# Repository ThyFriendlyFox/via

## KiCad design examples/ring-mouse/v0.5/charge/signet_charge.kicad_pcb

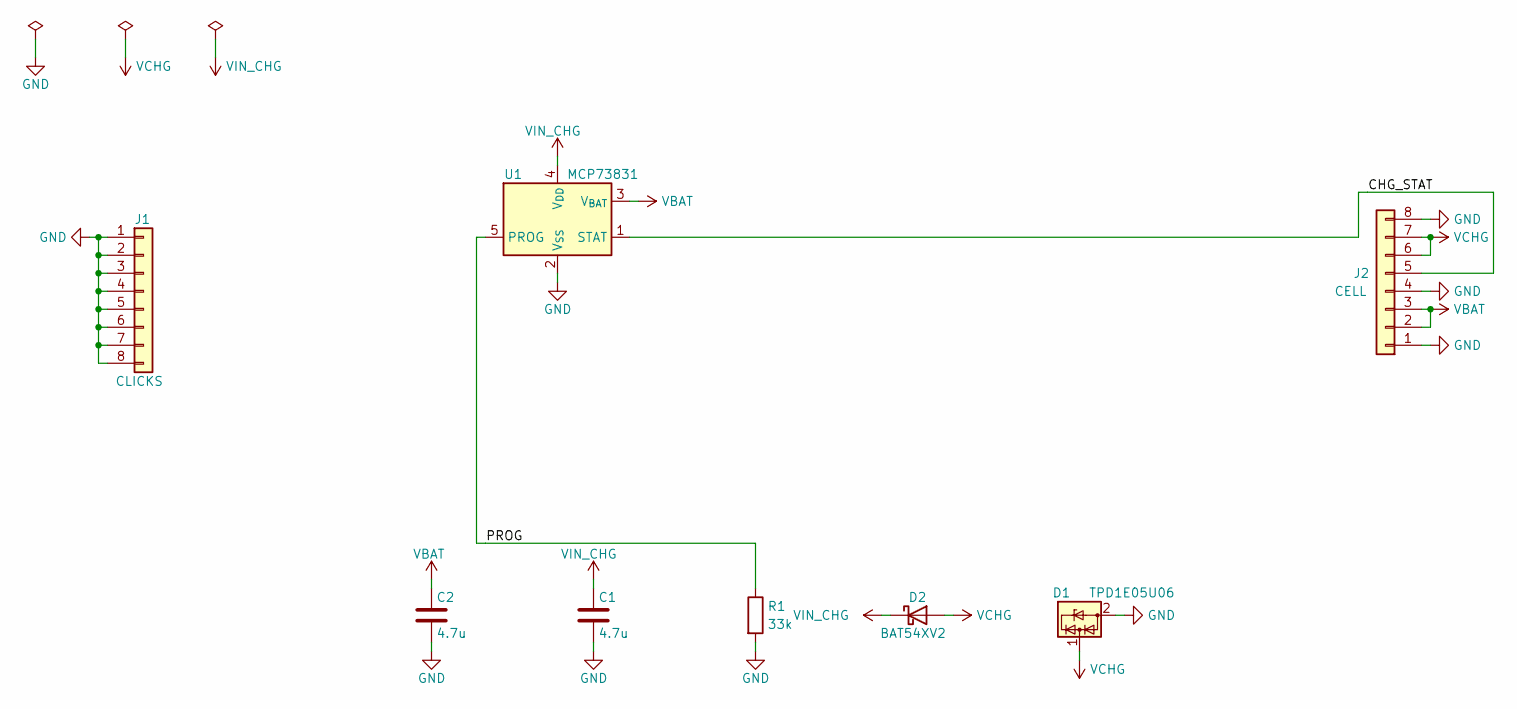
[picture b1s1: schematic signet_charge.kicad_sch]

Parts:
C1, C2: 4.7u; C_0402_1005Metric
D1: TPD1E05U06; D_SOD-523
D2: BAT54XV2; D_SOD-523
J1: CLICKS; Joint_Edge_1x08_P1.3mm
J2: CELL; Joint_Edge_1x08_P1.3mm
R1: 33k; R_0402_1005Metric
U1: MCP73831; SOT-23-5

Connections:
/CHG_STAT: J2.5, U1.1 (STAT)
/PROG: R1.1, U1.5 (PROG)
GND: C1.2, C2.2, D1.2 (GND), J1.1, J1.2, J1.3, J1.4, J1.5, J1.6, J1.7, J1.8, J2.1, J2.4, J2.8, R1.2, U1.2 (V_{SS})
VBAT: C2.1, J2.2, J2.3, U1.3 (V_{BAT})
VCHG: D1.1 (I/O), D2.2 (A), J2.6, J2.7
VIN_CHG: C1.1, D2.1 (K), U1.4 (V_{DD})

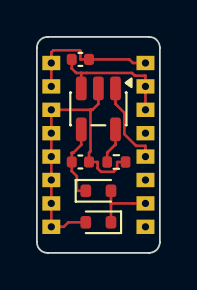
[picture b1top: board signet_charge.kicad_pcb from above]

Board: 4 copper layers, 6.8 x 12.0 mm, 8 parts (0 on the bottom side), 6 nets.

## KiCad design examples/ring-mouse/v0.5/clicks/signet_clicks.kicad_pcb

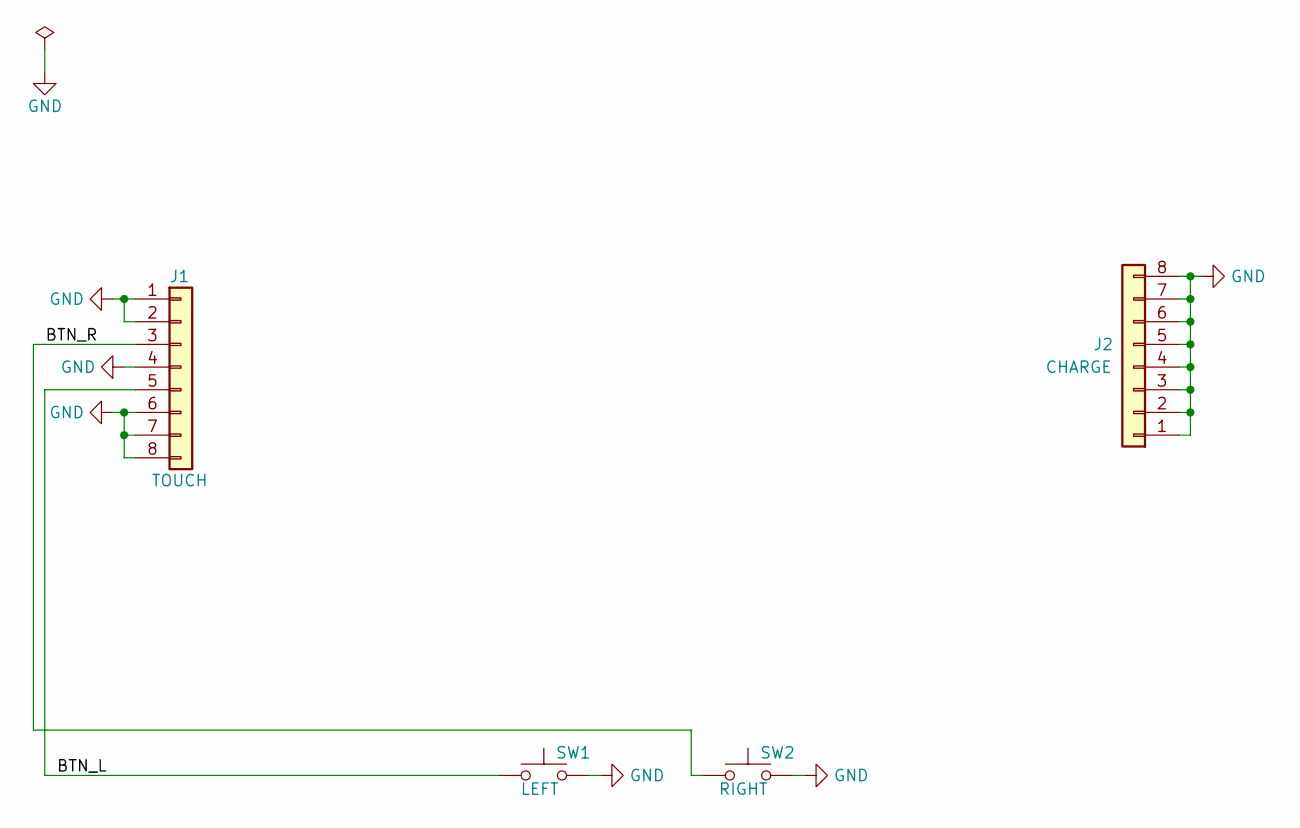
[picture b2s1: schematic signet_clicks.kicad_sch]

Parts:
J1: TOUCH; Joint_Edge_1x08_P1.3mm
J2: CHARGE; Joint_Edge_1x08_P1.3mm
SW1: LEFT; SW_Push_1P1T_NO_CK_KMR2
SW2: RIGHT; SW_Push_1P1T_NO_CK_KMR2

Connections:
/BTN_L: J1.5, SW1.1
/BTN_R: J1.3, SW2.1
GND: J1.1, J1.2, J1.4, J1.6, J1.7, J1.8, J2.1, J2.2, J2.3, J2.4, J2.5, J2.6, J2.7, J2.8, SW1.2, SW2.2

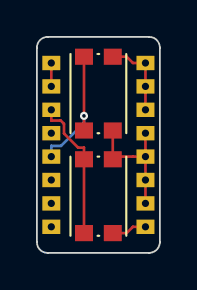
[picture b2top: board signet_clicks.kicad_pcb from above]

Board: 4 copper layers, 6.8 x 12.0 mm, 4 parts (0 on the bottom side), 3 nets.

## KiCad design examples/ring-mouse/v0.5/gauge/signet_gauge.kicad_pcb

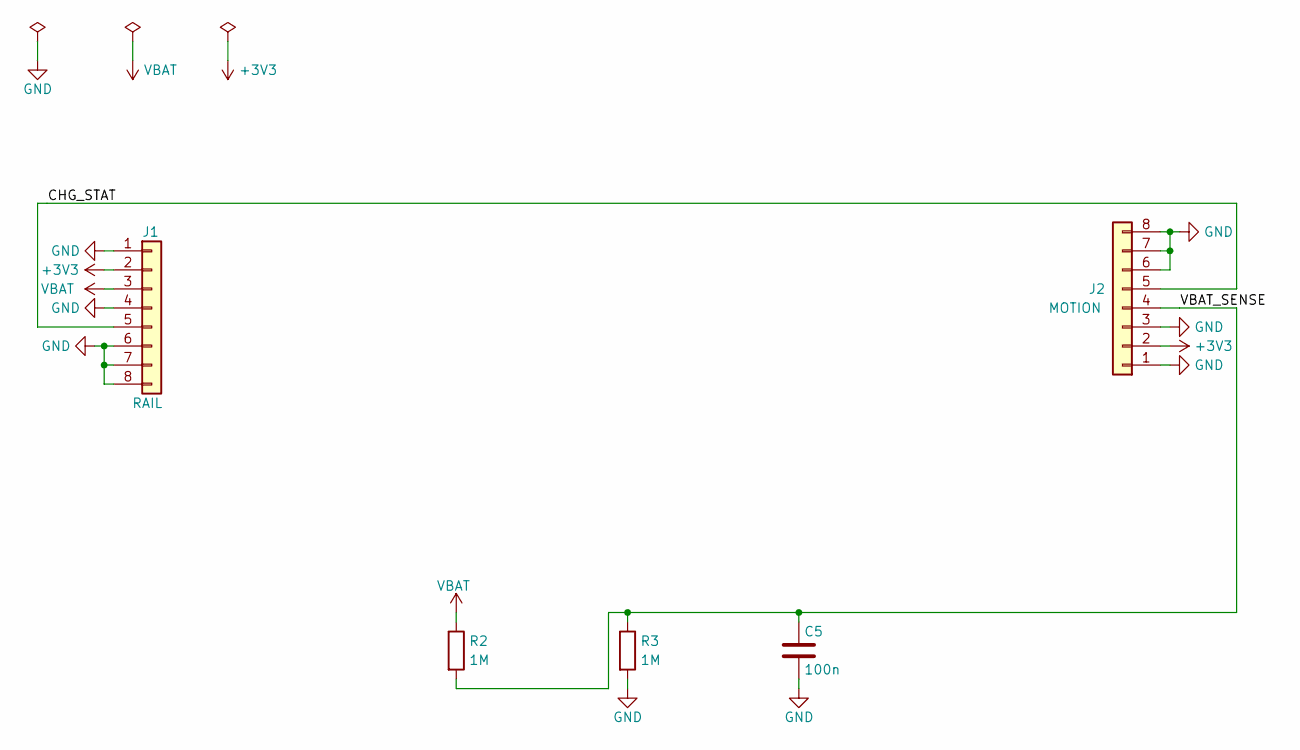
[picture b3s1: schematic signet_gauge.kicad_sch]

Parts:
C5: 100n; C_0402_1005Metric
J1: RAIL; Joint_Edge_1x08_P1.3mm
J2: MOTION; Joint_Edge_1x08_P1.3mm
R2, R3: 1M; R_0402_1005Metric

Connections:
+3V3: J1.2, J2.2
/CHG_STAT: J1.5, J2.5
/VBAT_SENSE: C5.1, J2.4, R2.2, R3.1
GND: C5.2, J1.1, J1.4, J1.6, J1.7, J1.8, J2.1, J2.3, J2.6, J2.7, J2.8, R3.2
VBAT: J1.3, R2.1

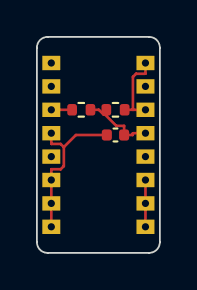
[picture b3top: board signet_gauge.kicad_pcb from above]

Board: 4 copper layers, 6.8 x 12.0 mm, 5 parts (0 on the bottom side), 5 nets.

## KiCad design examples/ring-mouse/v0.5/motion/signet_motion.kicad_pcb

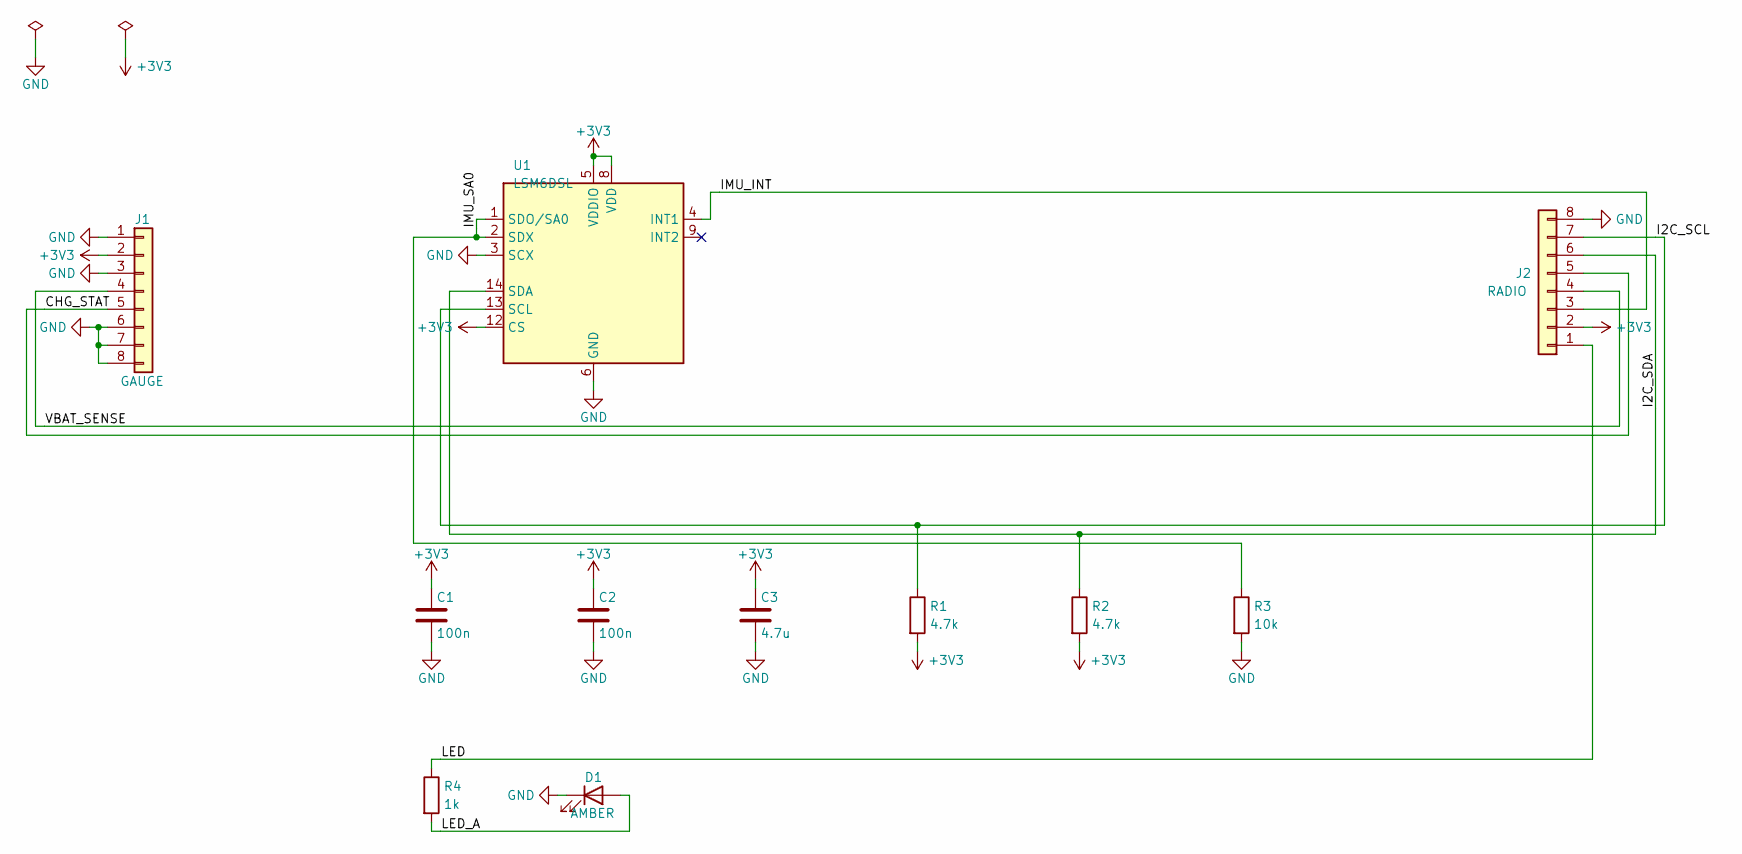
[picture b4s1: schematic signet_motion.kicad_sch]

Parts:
C1, C2: 100n; C_0402_1005Metric
C3: 4.7u; C_0402_1005Metric
D1: AMBER; LED_0402_1005Metric
J1: GAUGE; Joint_Edge_1x08_P1.3mm
J2: RADIO; Joint_Edge_1x08_P1.3mm
R1, R2: 4.7k; R_0402_1005Metric
R3: 10k; R_0402_1005Metric
R4: 1k; R_0402_1005Metric
U1: LSM6DSL; LGA-14_3x2.5mm_P0.5mm_LayoutBorder3x4y

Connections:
+3V3: C1.1, C2.1, C3.1, J1.2, J2.2, R1.2, R2.2, U1.5 (VDDIO), U1.8 (VDD), U1.12 (CS)
/CHG_STAT: J1.5, J2.5
/I2C_SCL: J2.7, R1.1, U1.13 (SCL)
/I2C_SDA: J2.6, R2.1, U1.14 (SDA)
/IMU_INT: J2.3, U1.4 (INT1)
/IMU_SA0: R3.1, U1.1 (SDO/SA0), U1.2 (SDX)
/LED: J2.1, R4.1
/LED_A: D1.2 (A), R4.2
/VBAT_SENSE: J1.4, J2.4
GND: C1.2, C2.2, C3.2, D1.1 (K), J1.1, J1.3, J1.6, J1.7, J1.8, J2.8, R3.2, U1.3 (SCX), U1.6 (GND), U1.7 (GND)

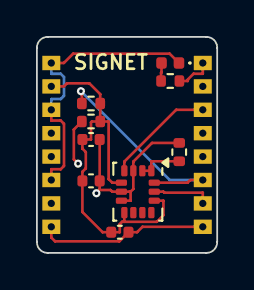
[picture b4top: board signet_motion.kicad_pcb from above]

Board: 4 copper layers, 10.0 x 12.0 mm, 11 parts (0 on the bottom side), 10 nets.

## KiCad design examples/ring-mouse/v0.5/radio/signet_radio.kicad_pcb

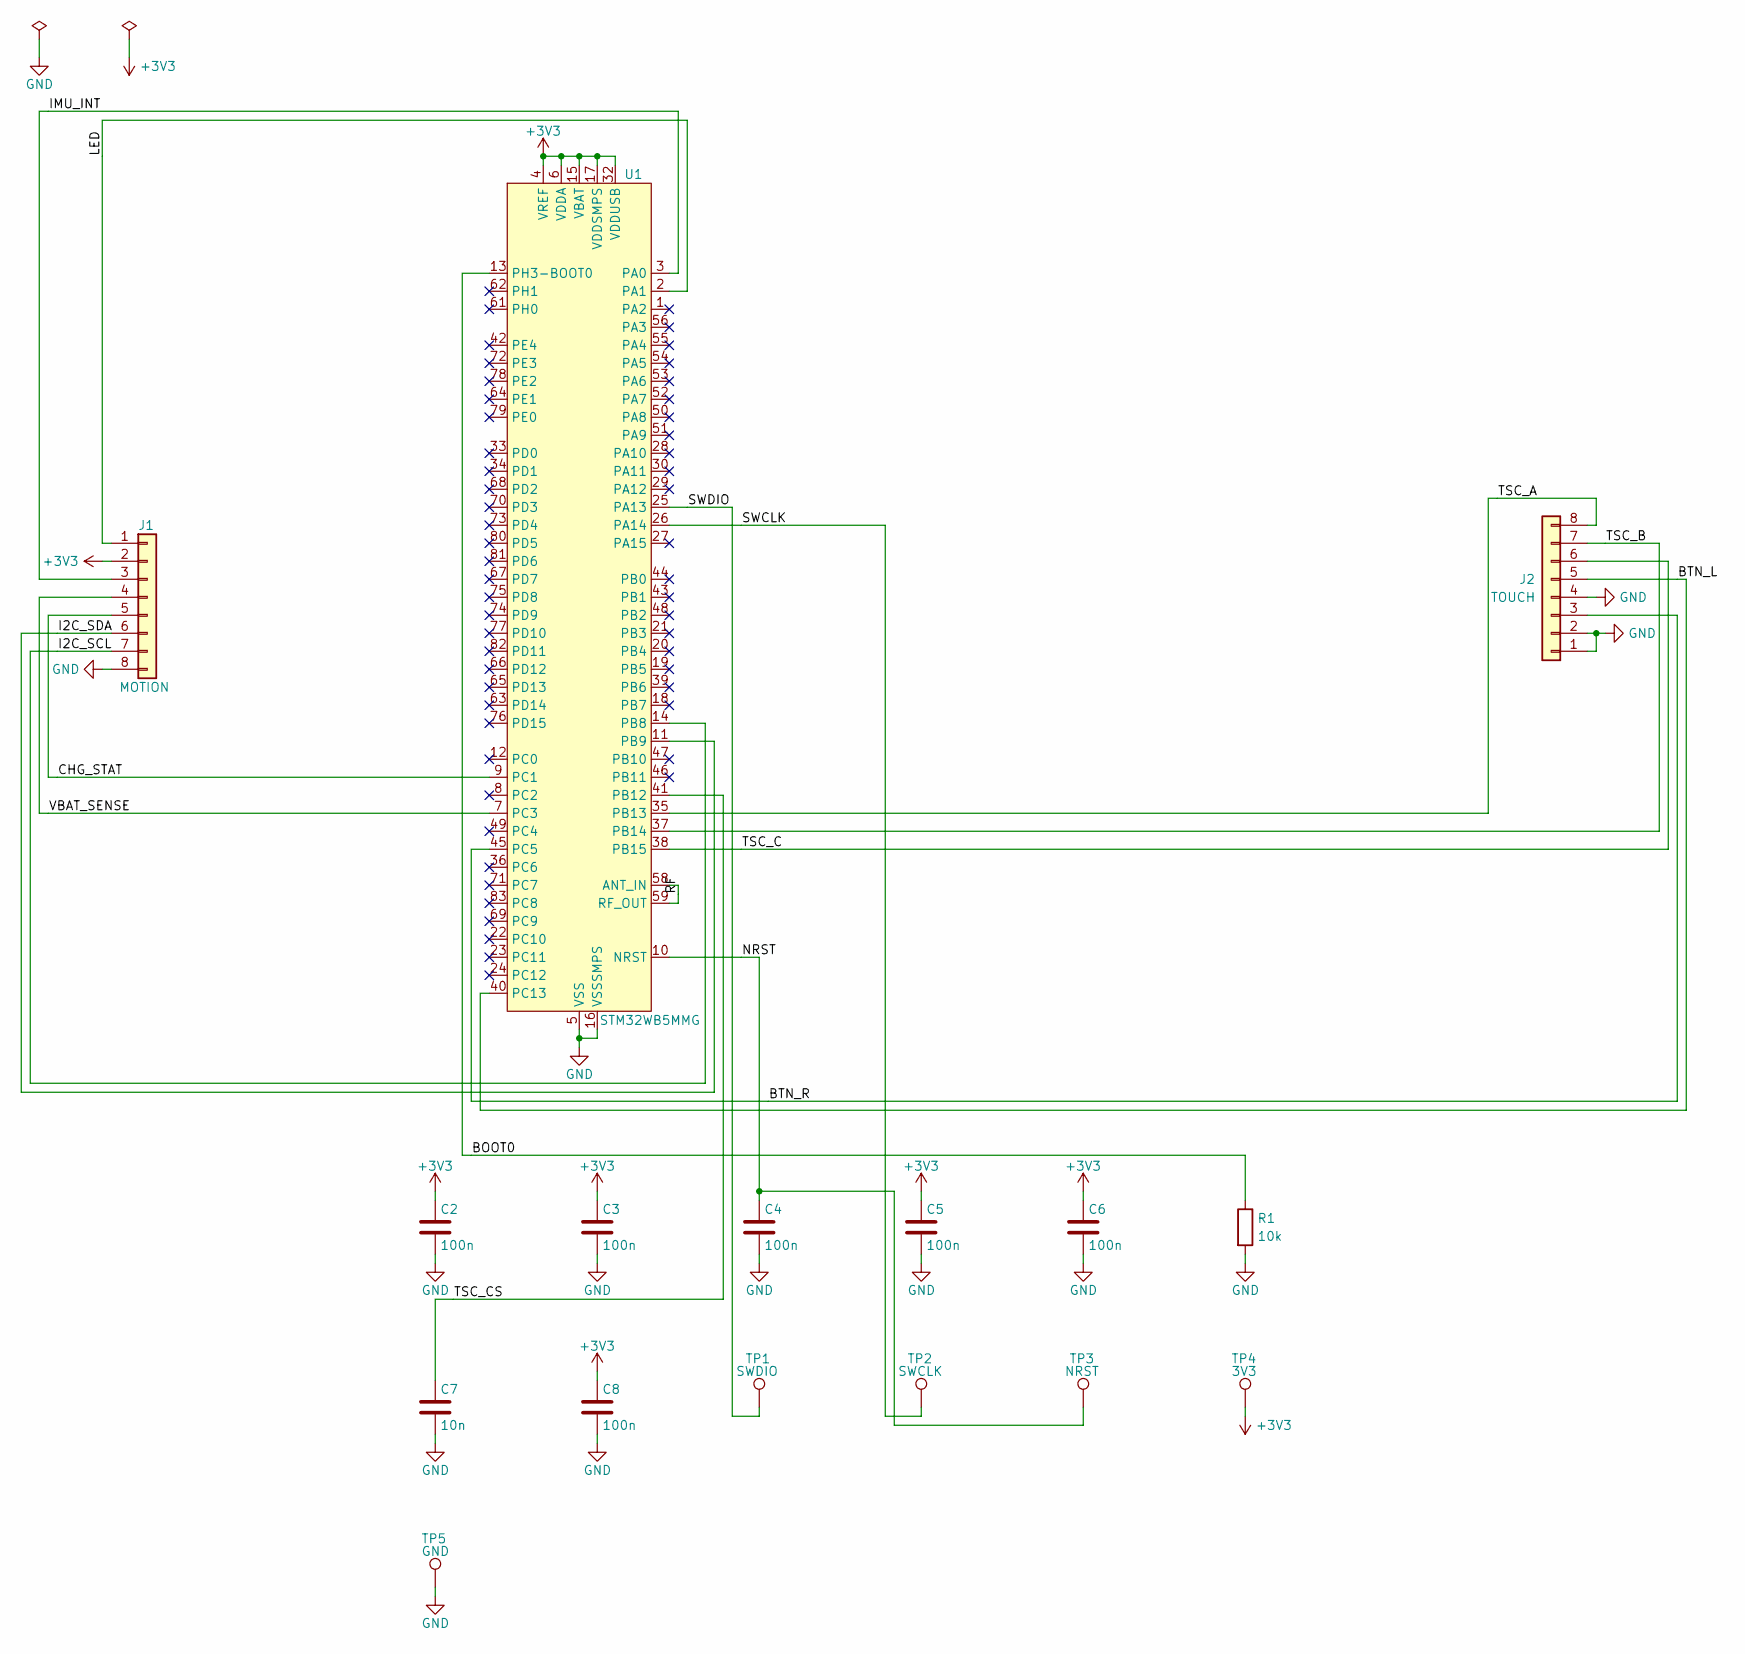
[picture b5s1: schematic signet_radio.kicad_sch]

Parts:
C2, C3, C4, C5, C6, C8: 100n; C_0201_0603Metric
C7: 10n; C_0201_0603Metric
J1: MOTION; Joint_Edge_1x08_P1.3mm
J2: TOUCH; Joint_Edge_1x08_P1.3mm
R1: 10k; R_0201_0603Metric
TP1: SWDIO; TestPoint_Pad_D1.0mm
TP2: SWCLK; TestPoint_Pad_D1.0mm
TP3: NRST; TestPoint_Pad_D1.0mm
TP4: 3V3; TestPoint_Pad_D1.0mm
TP5: GND; TestPoint_Pad_D1.0mm
U1: STM32WB5MMG; ST-SiP-LGA-86-11x7.3mm

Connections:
+3V3: C2.1, C3.1, C5.1, C6.1, C8.1, J1.2, TP4.1, U1.4 (VREF), U1.6 (VDDA), U1.15 (VBAT), U1.17 (VDDSMPS), U1.32 (VDDUSB)
/BOOT0: R1.1, U1.13 (PH3-BOOT0)
/BTN_L: J2.5, U1.40 (PC13)
/BTN_R: J2.3, U1.45 (PC5)
/CHG_STAT: J1.5, U1.9 (PC1)
/I2C_SCL: J1.7, U1.14 (PB8)
/I2C_SDA: J1.6, U1.11 (PB9)
/IMU_INT: J1.3, U1.3 (PA0)
/LED: J1.1, U1.2 (PA1)
/NRST: C4.1, TP3.1, U1.10 (NRST)
/RF: U1.58 (ANT_IN), U1.59 (RF_OUT)
/SWCLK: TP2.1, U1.26 (PA14)
/SWDIO: TP1.1, U1.25 (PA13)
/TSC_A: J2.8, U1.35 (PB13)
/TSC_B: J2.7, U1.37 (PB14)
/TSC_C: J2.6, U1.38 (PB15)
/TSC_CS: C7.1, U1.41 (PB12)
/VBAT_SENSE: J1.4, U1.7 (PC3)
GND: C2.2, C3.2, C4.2, C5.2, C6.2, C7.2, C8.2, J1.8, J2.1, J2.2, J2.4, R1.2, TP5.1, U1.5 (VSS), U1.16 (VSSSMPS), U1.31 (VSS), U1.57 (VSS), U1.60 (VSS), U1.84 (VSS), U1.86 (VSS)

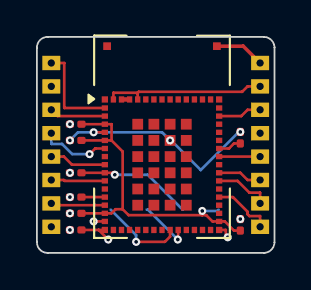
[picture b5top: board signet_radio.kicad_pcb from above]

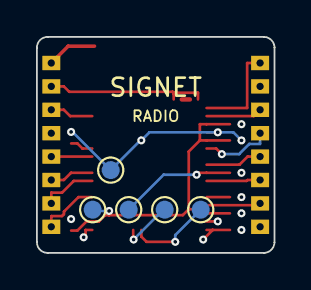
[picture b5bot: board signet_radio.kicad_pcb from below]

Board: 4 copper layers, 13.2 x 12.0 mm, 16 parts (5 on the bottom side), 19 nets.

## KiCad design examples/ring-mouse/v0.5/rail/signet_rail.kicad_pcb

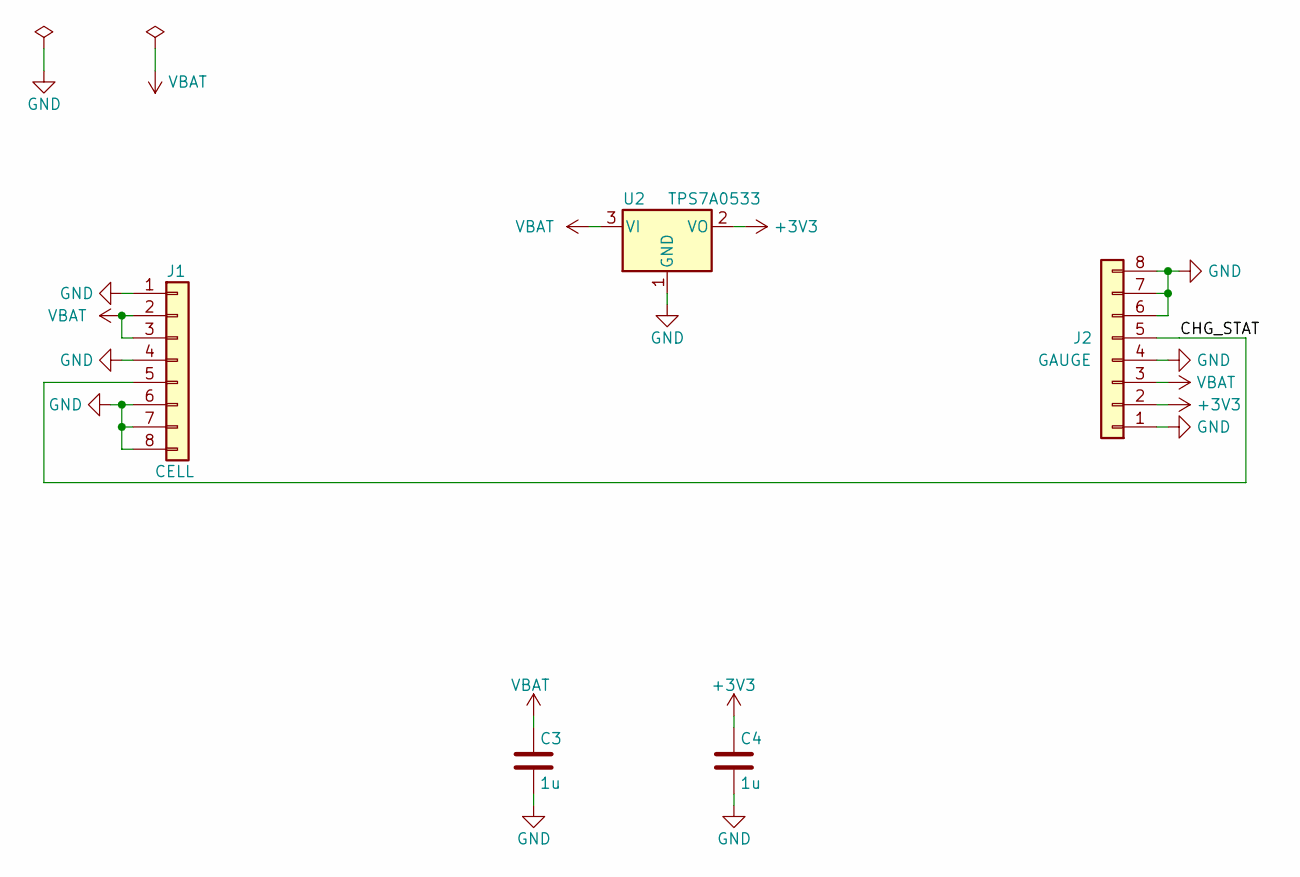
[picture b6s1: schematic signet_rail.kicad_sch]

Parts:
C3, C4: 1u; C_0402_1005Metric
J1: CELL; Joint_Edge_1x08_P1.3mm
J2: GAUGE; Joint_Edge_1x08_P1.3mm
U2: TPS7A0533; SOT-23-3

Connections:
+3V3: C4.1, J2.2, U2.2 (VO)
/CHG_STAT: J1.5, J2.5
GND: C3.2, C4.2, J1.1, J1.4, J1.6, J1.7, J1.8, J2.1, J2.4, J2.6, J2.7, J2.8, U2.1 (GND)
VBAT: C3.1, J1.2, J1.3, J2.3, U2.3 (VI)

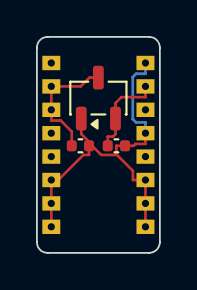
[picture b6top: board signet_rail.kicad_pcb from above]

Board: 4 copper layers, 6.8 x 12.0 mm, 5 parts (0 on the bottom side), 4 nets.

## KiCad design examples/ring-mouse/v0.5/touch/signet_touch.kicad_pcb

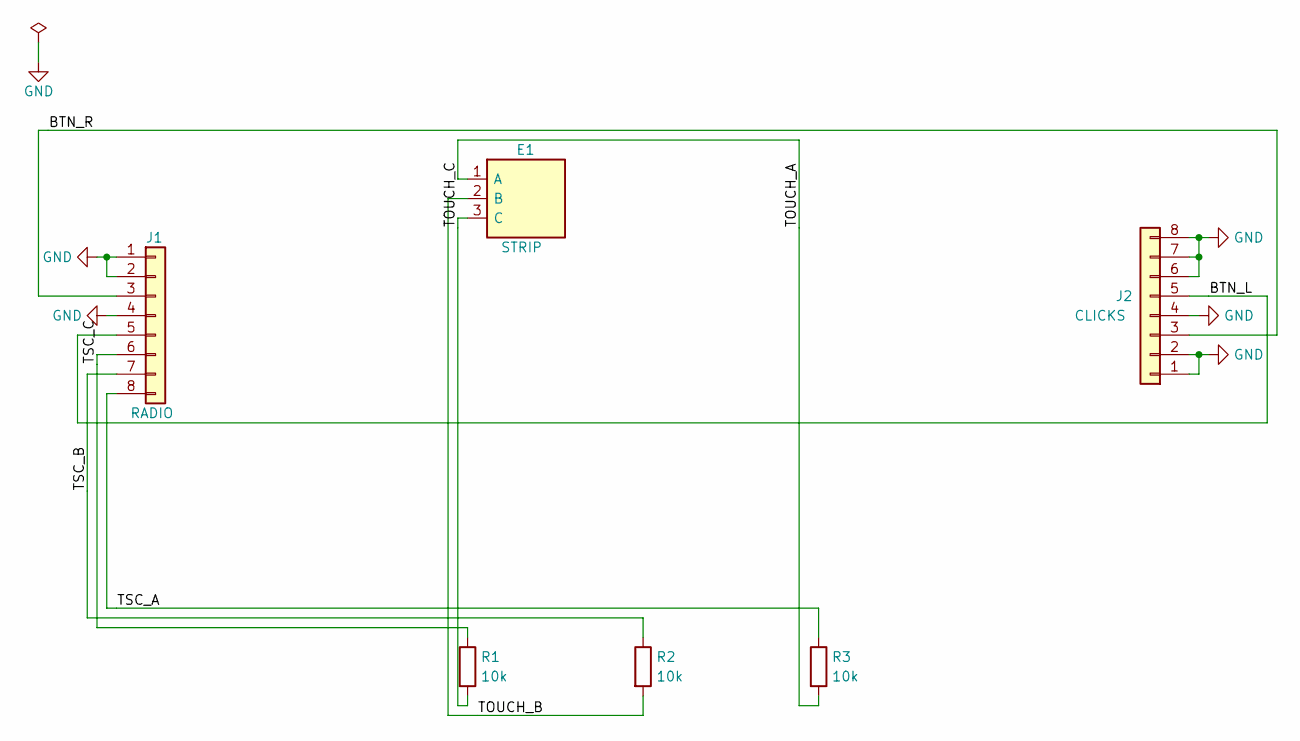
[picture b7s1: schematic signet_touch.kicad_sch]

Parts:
E1: STRIP; TouchStrip_3ch_6x
J1: RADIO; Joint_Edge_1x08_P1.3mm
J2: CLICKS; Joint_Edge_1x08_P1.3mm
R1, R2, R3: 10k; R_0402_1005Metric

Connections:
/BTN_L: J1.5, J2.5
/BTN_R: J1.3, J2.3
/TOUCH_A: E1.1 (A), R3.2
/TOUCH_B: E1.2 (B), R2.2
/TOUCH_C: E1.3 (C), R1.2
/TSC_A: J1.8, R3.1
/TSC_B: J1.7, R2.1
/TSC_C: J1.6, R1.1
GND: J1.1, J1.2, J1.4, J2.1, J2.2, J2.4, J2.6, J2.7, J2.8

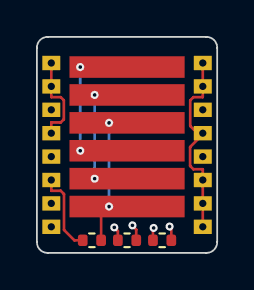
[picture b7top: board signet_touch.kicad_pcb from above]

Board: 4 copper layers, 10.0 x 12.0 mm, 6 parts (0 on the bottom side), 9 nets.
